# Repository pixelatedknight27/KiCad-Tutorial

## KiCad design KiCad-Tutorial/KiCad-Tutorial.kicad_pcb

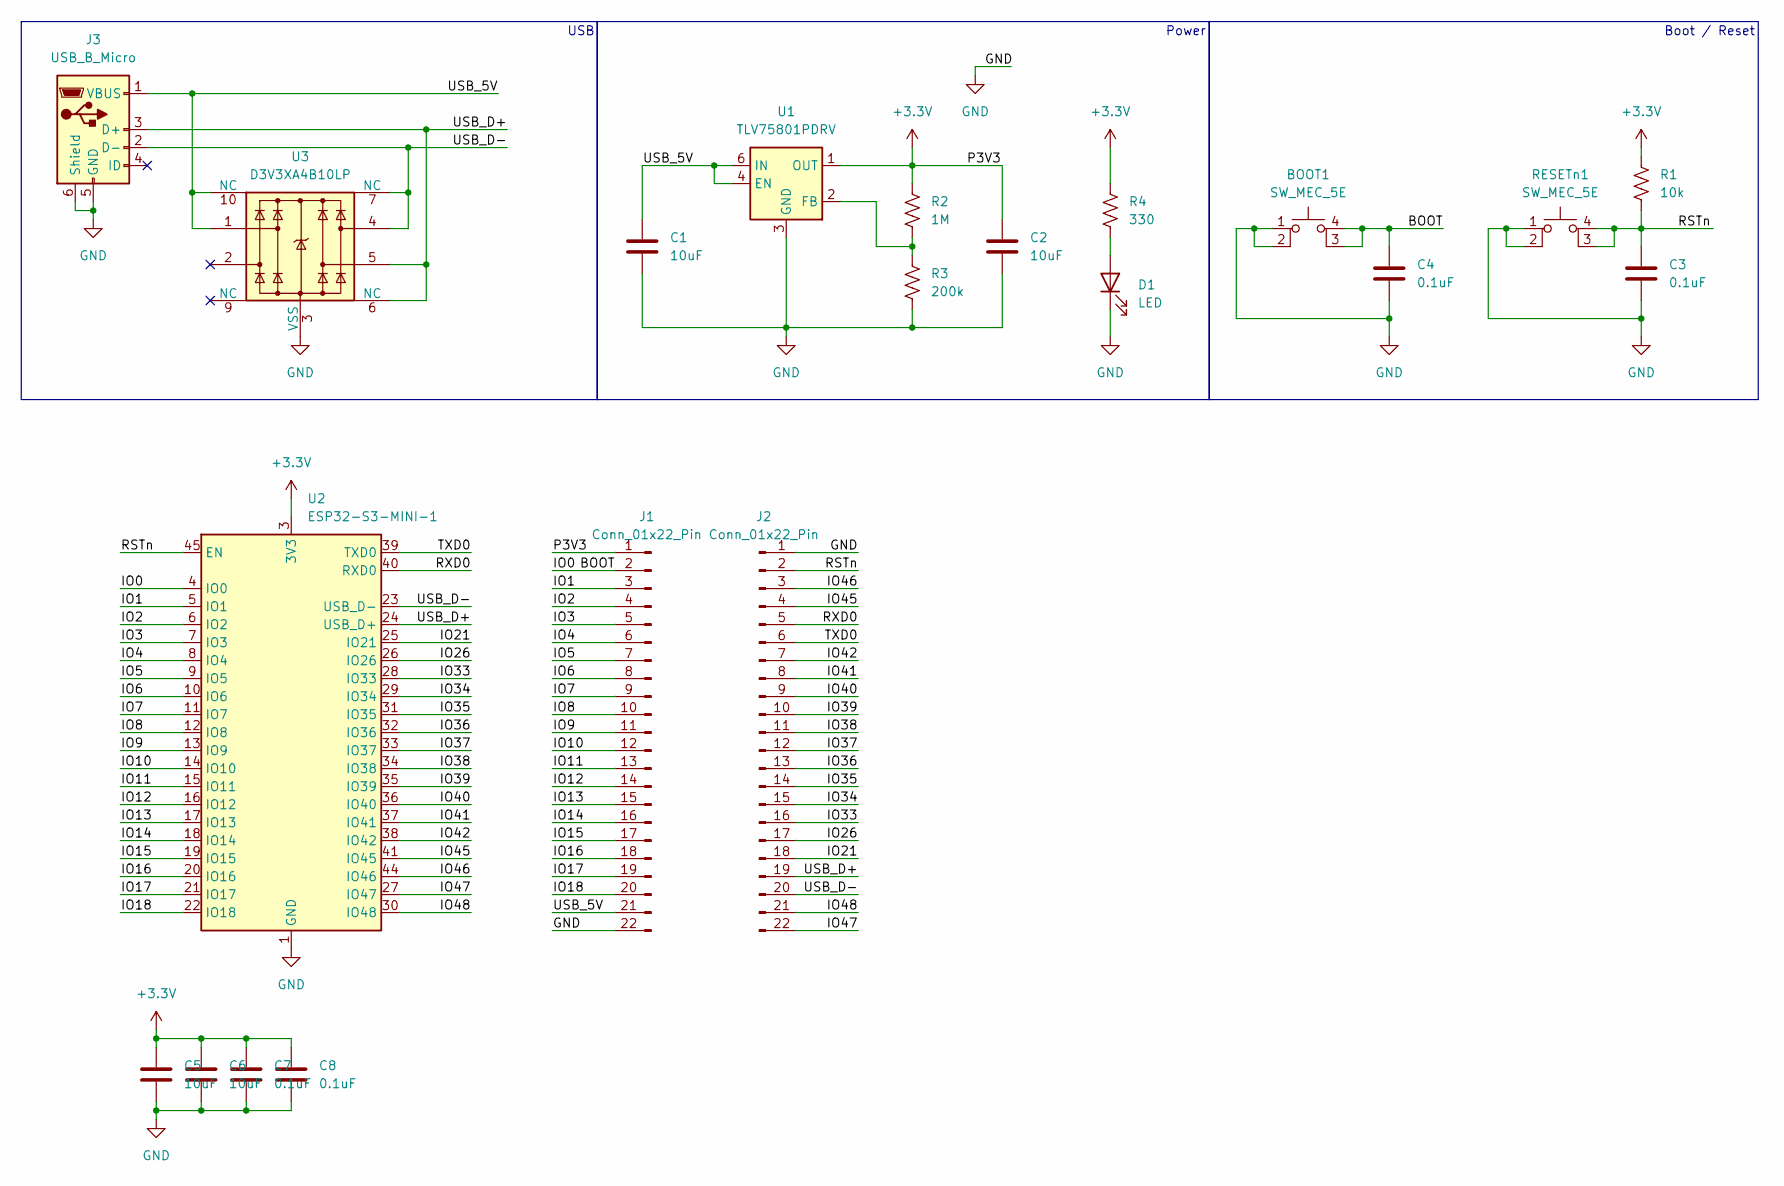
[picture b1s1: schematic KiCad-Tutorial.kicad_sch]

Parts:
BOOT1: SW_MEC_5E; SW_SPST_PTS810
C1, C2, C5, C6: 10uF; C_0603_1608Metric
C3, C4, C7, C8: 0.1uF; C_0603_1608Metric
D1: LED; LED_0603_1608Metric
J1, J2: Conn_01x22_Pin; PinHeader_1x22_P2.54mm_Vertical
J3: USB_B_Micro; USB_Micro-B_Molex-105017-0001
R1: 10k; R_0603_1608Metric
R2: 1M; R_0603_1608Metric
R3: 200k; R_0603_1608Metric
R4: 330; R_0603_1608Metric
RESETn1: SW_MEC_5E; SW_SPST_PTS810
U1: TLV75801PDRV; WSON-6-1EP_2x2mm_P0.65mm_EP1x1.6mm
U2: ESP32-S3-MINI-1; ESP32-S2-MINI-1
U3: D3V3XA4B10LP; Diodes_UDFN-10_1.0x2.5mm_P0.5mm

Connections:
+3.3V: C2.1, C5.1, C6.1, C7.1, C8.1, J1.1, R1.1, R2.1, R4.1, U1.1 (OUT), U2.3 (3V3)
/BOOT: BOOT1.3 (K), BOOT1.4 (A), C4.1, J1.2, U2.4 (IO0)
/IO1: J1.3, U2.5 (IO1)
/IO2: J1.4, U2.6 (IO2)
/IO3: J1.5, U2.7 (IO3)
/IO4: J1.6, U2.8 (IO4)
/IO5: J1.7, U2.9 (IO5)
/IO6: J1.8, U2.10 (IO6)
/IO7: J1.9, U2.11 (IO7)
/IO8: J1.10, U2.12 (IO8)
/IO9: J1.11, U2.13 (IO9)
/IO10: J1.12, U2.14 (IO10)
/IO11: J1.13, U2.15 (IO11)
/IO12: J1.14, U2.16 (IO12)
/IO13: J1.15, U2.17 (IO13)
/IO14: J1.16, U2.18 (IO14)
/IO15: J1.17, U2.19 (IO15)
/IO16: J1.18, U2.20 (IO16)
/IO17: J1.19, U2.21 (IO17)
/IO18: J1.20, U2.22 (IO18)
/IO21: J2.18, U2.25 (IO21)
/IO26: J2.17, U2.26 (IO26)
/IO33: J2.16, U2.28 (IO33)
/IO34: J2.15, U2.29 (IO34)
/IO35: J2.14, U2.31 (IO35)
/IO36: J2.13, U2.32 (IO36)
/IO37: J2.12, U2.33 (IO37)
/IO38: J2.11, U2.34 (IO38)
/IO39: J2.10, U2.35 (IO39)
/IO40: J2.9, U2.36 (IO40)
/IO41: J2.8, U2.37 (IO41)
/IO42: J2.7, U2.38 (IO42)
/IO45: J2.4, U2.41 (IO45)
/IO46: J2.3, U2.44 (IO46)
/IO47: J2.22, U2.27 (IO47)
/IO48: J2.21, U2.30 (IO48)
/RSTn: C3.1, J2.2, R1.2, RESETn1.3 (K), RESETn1.4 (A), U2.45 (EN)
/RXD0: J2.5, U2.40 (RXD0)
/TXD0: J2.6, U2.39 (TXD0)
/USB_5V: C1.1, J1.21, J3.1 (VBUS), U1.4 (EN), U1.6 (IN), U3.1, U3.10 (NC)
/USB_D+: J2.19, J3.3 (D+), U2.24 (USB_D+), U3.5, U3.6 (NC)
/USB_D-: J2.20, J3.2 (D-), U2.23 (USB_D-), U3.4, U3.7 (NC)
GND: BOOT1.1, BOOT1.2, C1.2, C2.2, C3.2, C4.2, C5.2, C6.2, C7.2, C8.2, D1.1 (K), J1.22, J2.1, J3.5 (GND), J3.6 (Shield), R3.2, RESETn1.1, RESETn1.2, U1.3 (GND), U1.7 (GND), U2.1 (GND), U2.2 (GND), U2.42 (GND), U2.43 (GND), U2.46 (GND), U2.47 (GND), U2.48 (GND), U2.49 (GND), U2.50 (GND), U2.51 (GND), U2.52 (GND), U2.53 (GND), U2.54 (GND), U2.55 (GND), U2.56 (GND), U2.57 (GND), U2.58 (GND), U2.59 (GND), U2.60 (GND), U2.61 (GND), U2.62 (GND), U2.63 (GND), U2.64 (GND), U2.65 (GND), U3.3 (VSS), U3.8 (VSS)
unnamed: D1.2 (A), R4.2
unnamed: R2.2, R3.1, U1.2 (FB)

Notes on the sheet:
Boot / Reset
Power
USB

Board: 4 copper layers, 21 parts (8 on the bottom side), 45 nets, no tracks yet.

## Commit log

2025-03-03 Basic Setup
2025-03-03 Removed Prod and moved 3D Model folder
2025-03-03 edited the path of the 3d models
2025-03-24 Example Done
2025-04-02 Whoops
